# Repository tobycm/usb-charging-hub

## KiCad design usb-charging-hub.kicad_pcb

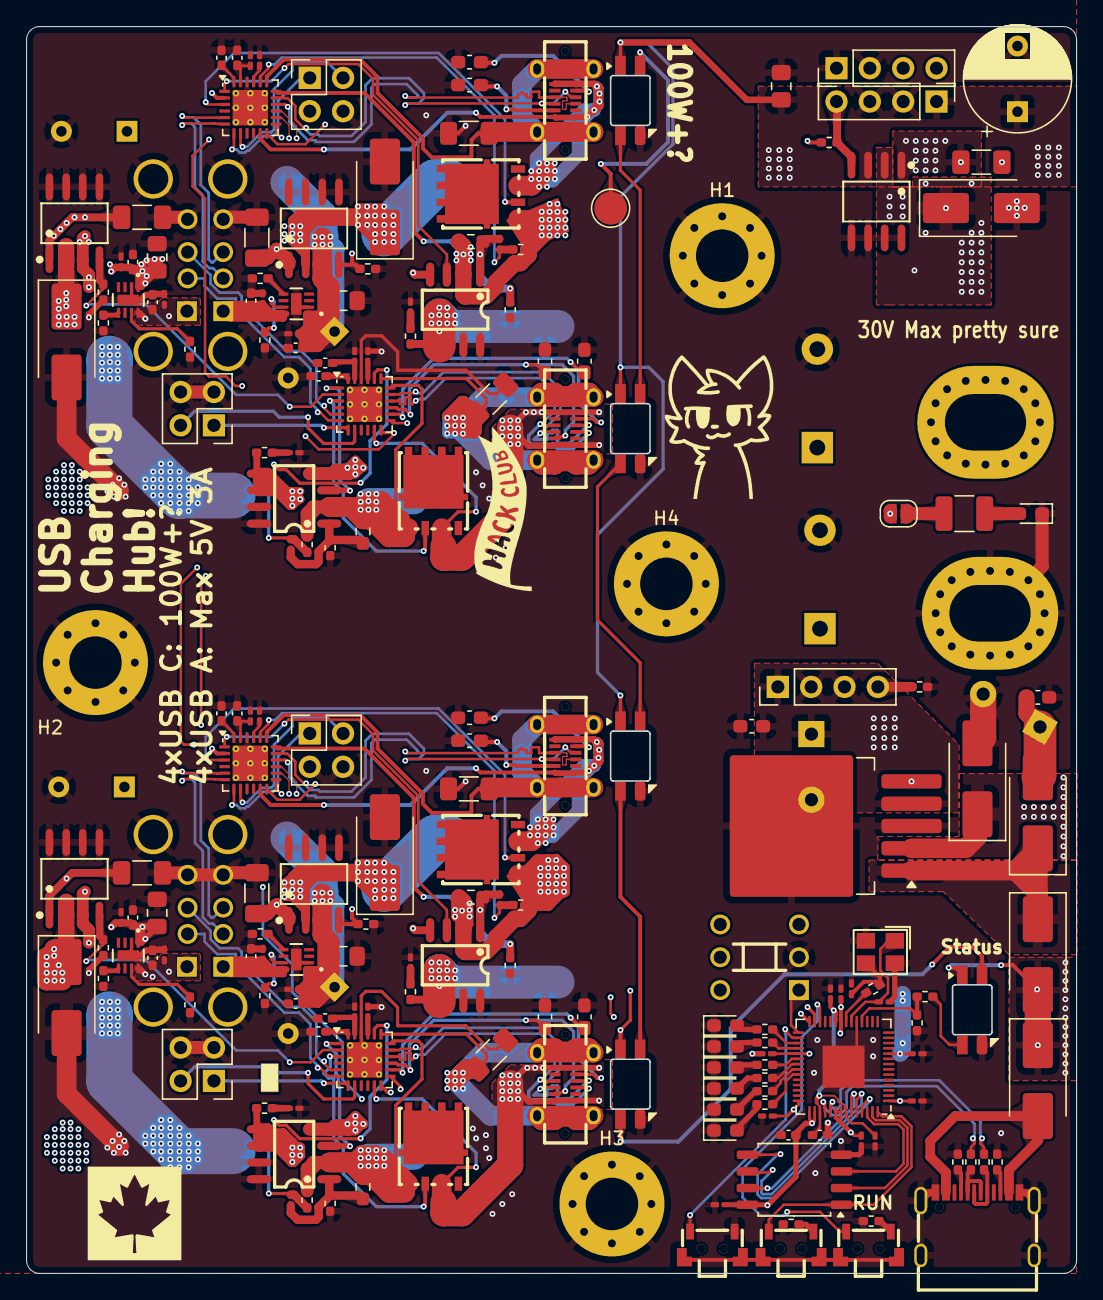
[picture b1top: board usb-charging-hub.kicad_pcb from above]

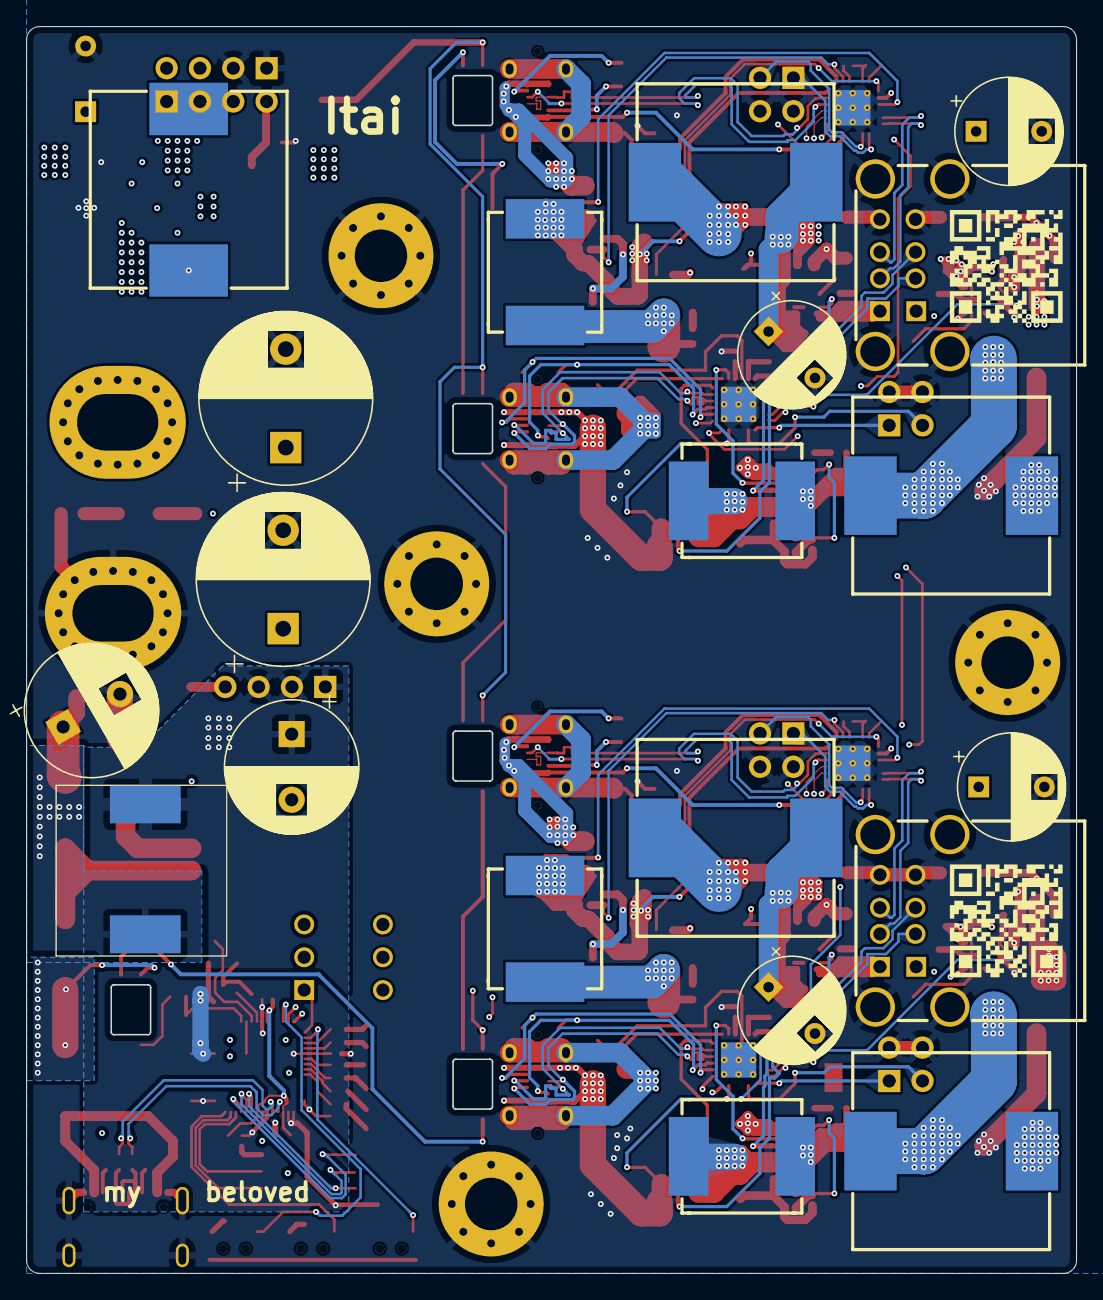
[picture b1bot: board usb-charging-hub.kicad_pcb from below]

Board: 4 copper layers, 80.0 x 95.0 mm, 214 parts (20 on the bottom side), 159 nets.

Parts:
C1, C2: 50V,1000uF; CP_Radial_D13.0mm_P7.50mm
C3, C4, C5, C7, C8, C9, C10, C11, C12, C29, C36, C38, C40, C42, C44, C45, C52, C59, C66, C68, C70, C72, C74, C75, C82: 100nF; C_0201_0603Metric_Pad0.64x0.40mm_HandSolder
C6, C13, C30, C31, C37, C39, C41, C43, C46, C47, C60, C61, C67, C69, C71, C73, C76, C77: 1uF; C_0402_1005Metric_Pad0.74x0.62mm_HandSolder
C14, C15: 18pF; C_0201_0603Metric_Pad0.64x0.40mm_HandSolder
C16: 50V,470uF; CP_Radial_D10.0mm_P5.00mm
C17: 50V,1uF; C_0603_1608Metric_Pad1.08x0.95mm_HandSolder
C18: 35V,470uF; CP_Radial_D10.0mm_P5.00mm
C19: 10V,10uF; C_0603_1608Metric_Pad1.08x0.95mm_HandSolder
C20, C23, C24, C53, C54: 50V,10uF; C_1206_3216Metric_Pad1.33x1.80mm_HandSolder
C21, C25, C27, C55, C57: 35V,180uF; CP_Radial_D8.0mm_P5.00mm
C22, C26, C28, C56, C58: 35V,22uF; C_0805_2012Metric_Pad1.18x1.45mm_HandSolder
C32, C33, C48, C49, C62, C63, C78, C79: 390pF 5% X7R; C_0603_1608Metric_Pad1.08x0.95mm_HandSolder
C34, C50, C64, C80: 100pF; C_0201_0603Metric_Pad0.64x0.40mm_HandSolder
C35, C51, C65, C81: 1nF; C_0201_0603Metric_Pad0.64x0.40mm_HandSolder
D1: LED; LED_0603_1608Metric_Pad1.05x0.95mm_HandSolder
D2, D3: Green; LED_0603_1608Metric_Pad1.05x0.95mm_HandSolder
D4, D9, D11, D12, D13, D14, D15, D16: 40V,10A; D_SMB_Handsoldering
D5, D6: Amber; LED_0603_1608Metric_Pad1.05x0.95mm_HandSolder
D7, D8: Red; LED_0603_1608Metric_Pad1.05x0.95mm_HandSolder
D10: 60V,10A; D_SMB_Handsoldering
H1, H2, H3, H4: MountingHole_Pad; MountingHole_4mm_Pad_Via
J1, J2: Conn_01x01_Pin; MountingHole_4.3x6.2mm_M4_Pad_Via
J4, J6, J7: Conn_01x04_Pin; PinHeader_1x04_P2.54mm_Vertical
J8, J11, J13, J16: TYPE-C 16PLT-H10.0; TYPE-C-SMD_USB4120-03-C
J9, J12, J14, J17: Conn_01x04_Pin; PinHeader_2x02_P2.54mm_Vertical
J10, J15: XDUF-0426-081_C18202150; USB-A-TH_XDUF-0426-081
J35: GT-USB-7010ASV; USB-C-SMD_G-SWITCH_GT-USB-7010ASV
JP1: SolderJumper_2_Open; SolderJumper-2_P1.3mm_Open_RoundedPad1.0x1.5mm
L1: 33uH,4.25A; SDRI129-330MT
L2, L3, L4, L7, L8: YPRH1508-680M; IND-SMD_L15.0-W15.0
L5, L6, L9, L10: 6.8uH,5.2A,8A(Isat); IND-SMD_L8.0-W8.0-1
LED1, LED2, LED3, LED4, LED5: SK6812MINI-E_C5149201; SK6812-MINI-E
Q1, Q2, Q3, Q4: PMOS; PDFN-8_L5.2-W5.9-P1.27-LS6.2-BL
R1: 1.5k; R_1210_3225Metric_Pad1.30x2.65mm_HandSolder
R2, R3: 5.1k; R_0402_1005Metric_Pad0.72x0.64mm_HandSolder
R4, R5: 27; R_0402_1005Metric_Pad0.72x0.64mm_HandSolder
R6, R11, R16, R22, R31, R38, R47: 1k; R_0402_1005Metric_Pad0.72x0.64mm_HandSolder
R9, R10, R12, R13, R14, R15, R107: 470; R_0402_1005Metric_Pad0.72x0.64mm_HandSolder
R17, R18, R19, R20, R35, R36: 100k; R_0402_1005Metric_Pad0.72x0.64mm_HandSolder
R21, R30, R37, R46: 40k; R_0603_1608Metric_Pad0.98x0.95mm_HandSolder
R23, R32, R39, R48: 6.8; R_0402_1005Metric_Pad0.72x0.64mm_HandSolder
R24, R27, R29, R33, R40, R43, R45, R49, R108: 10k; R_0402_1005Metric_Pad0.72x0.64mm_HandSolder
R25, R34, R41, R50: 5mOhm 1% Shunt; R_1206_3216Metric_Pad1.30x1.75mm_HandSolder
R26, R28, R42, R44: 249k; R_0402_1005Metric_Pad0.72x0.64mm_HandSolder
SW1, SW3, SW4: TS24CA; SW-SMD_TS24CA
SW2: Latching; SW-TH_6P-L8.0-W8.0-P2.50
TP1: TestPoint; TestPoint_Pad_D2.5mm
U1: W25Q32JVSS; SOIC-8_5.3x5.3mm_P1.27mm
U2: ABM8-272-T3_C20625731; CRYSTAL-SMD_4P-L3.2-W2.5-BL
U3: RP2040; QFN-56-1EP_7x7mm_P0.4mm_EP3.2x3.2mm
U4: LM2596S-3.3; TO-263-5_TabPin3
U5, U6, U7, U14, U15: XXL1509-5.0; SOIC-8_L4.9-W3.9-P1.27-LS6.0-BL
U8, U12, U16, U20: NDP23511KC; SOP-8_L4.9-W3.9-P1.27-LS6.0-BL
U9, U13, U17, U21: CYPD3175-24LQXQ; QFN-24-1EP_4x4mm_P0.5mm_EP2.7x2.7mm_ThermalVias
U10, U11, U18, U19: LS0505EVD22; LS0505EVD22_LTF

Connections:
3.3V_BUCK_EN: J4.4, R17.2, U4.5 (~ON/OFF)
5V_BUCK_EN: J6.4, R18.2, U5.4 (EN)
+1V1: C4.2, C5.2, C6.2, U3.23 (DVDD), U3.45 (VREG_VOUT), U3.50 (DVDD)
+3.3V: C3.2, C7.2, C8.2, C9.2, C10.2, C11.2, C12.2, C13.2, C18.1, C19.1, J4.1, J4.2, J4.3, L1.2, U1.8 (VCC), U3.1 (IOVDD), U3.10 (IOVDD), U3.22 (IOVDD), U3.33 (IOVDD), U3.42 (IOVDD), U3.43 (ADC_AVDD), U3.44 (VREG_IN), U3.48 (USB_VDD), U3.49 (IOVDD), U4.4 (FB)
+5V: C21.1, C22.1, D4.1 (K), D9.2 (A), J6.1, J6.2, J6.3, L2.2, LED1.1 (VDD), LED2.1 (VDD), LED3.1 (VDD), LED4.1 (VDD), LED5.1 (VDD), U5.3 (FB)
/USB 1/1_BUCK_EN: U8.3 (EN), U9.1 (P1.0)
/USB 1/1_D+: J8.A6 (DP1), J8.B6 (DP2), U9.17 (DP0/P3.0)
/USB 1/1_D-: J8.A7 (DN1), J8.B7 (DN2), U9.16 (DM0/P3.1)
/USB 1/2_BUCK_EN: U12.3 (EN), U13.1 (P1.0)
/USB 1/2_D+: J11.A6 (DP1), J11.B6 (DP2), U13.17 (DP0/P3.0)
/USB 1/2_D-: J11.A7 (DN1), J11.B7 (DN2), U13.16 (DM0/P3.1)
/USB 1/D_5V: C27.1, C28.1, C43.2, C44.2, L4.2, U7.3 (FB), U11.1 (IN)
/USB 1/D_BUCK_EN: R20.2, U7.4 (EN), U13.2 (P1.1)
/USB 1/D_D+: J10.7 (D-D+), U13.5 (DP1/P1.2)
/USB 1/D_D-: J10.6 (D-D-), U13.6 (DM1/P1.3)
/USB 1/D_EN: R29.1, U11.5 (EN)
/USB 1/U_5V: C25.1, C26.1, C39.2, C40.2, L3.2, U6.3 (FB), U10.1 (IN)
/USB 1/U_BUCK_EN: R19.2, U6.4 (EN), U9.2 (P1.1)
/USB 1/U_D+: J10.3 (U-D+), U9.5 (DP1/P1.2)
/USB 1/U_D-: J10.2 (U-D-), U9.6 (DM1/P1.3)
/USB 1/U_EN: R27.1, U10.5 (EN)
/USB 2/1_BUCK_EN: U16.3 (EN), U17.1 (P1.0)
/USB 2/1_D+: J13.A6 (DP1), J13.B6 (DP2), U17.17 (DP0/P3.0)
/USB 2/1_D-: J13.A7 (DN1), J13.B7 (DN2), U17.16 (DM0/P3.1)
/USB 2/2_BUCK_EN: U20.3 (EN), U21.1 (P1.0)
/USB 2/2_D+: J16.A6 (DP1), J16.B6 (DP2), U21.17 (DP0/P3.0)
/USB 2/2_D-: J16.A7 (DN1), J16.B7 (DN2), U21.16 (DM0/P3.1)
/USB 2/D_5V: C57.1, C58.1, C73.2, C74.2, L8.2, U15.3 (FB), U19.1 (IN)
/USB 2/D_BUCK_EN: R36.2, U15.4 (EN), U21.2 (P1.1)
/USB 2/D_D+: J15.7 (D-D+), U21.5 (DP1/P1.2)
/USB 2/D_D-: J15.6 (D-D-), U21.6 (DM1/P1.3)
/USB 2/D_EN: R45.1, U19.5 (EN)
/USB 2/U_5V: C55.1, C56.1, C69.2, C70.2, L7.2, U14.3 (FB), U18.1 (IN)
/USB 2/U_BUCK_EN: R35.2, U14.4 (EN), U17.2 (P1.1)
/USB 2/U_D+: J15.3 (U-D+), U17.5 (DP1/P1.2)
/USB 2/U_D-: J15.2 (U-D-), U17.6 (DM1/P1.3)
/USB 2/U_EN: R43.1, U18.5 (EN)
/rp2040/USB_D+: R4.2, U3.47 (USB_DP)
/rp2040/USB_D-: R5.2, U3.46 (USB_DM)
/rp2040/USB_R_D+: J35.A6 (DP1), J35.B6 (DP2), R4.1
/rp2040/USB_R_D-: J35.A7 (DN1), J35.B7 (DN2), R5.1
GND: C1.2, C2.2, C3.1, C4.1, C5.1, C6.1, C7.1, C8.1, C9.1, C10.1, C11.1, C12.1, C13.1, C14.1, C15.1, C16.2, C17.2, C18.2, C19.2, C20.2, C21.2, C22.2, C23.2, C24.2, C25.2, C26.2, C27.2, C28.2, C29.1, C30.1, C31.1, C32.2, C33.2, C35.2, C36.2, C37.1, C38.1, C39.1, C40.1, C41.1, C42.1, C43.1, C44.1, C45.1, C46.1, C47.1, C48.2, C49.2, C51.2, C52.2, C53.2, C54.2, C55.2, C56.2, C57.2, C58.2, C59.1, C60.1, C61.1, C62.2, C63.2, C65.2, C66.2, C67.1, C68.1, C69.1, C70.1, C71.1, C72.1, C73.1, C74.1, C75.1, C76.1, C77.1, C78.2, C79.2, C81.2, C82.2, D1.1 (K), D2.1 (K), D3.1 (K), D5.1 (K), D6.1 (K), D7.1 (K), D8.1 (K), D11.2 (A), D12.2 (A), D13.2 (A), D14.2 (A), D15.2 (A), D16.2 (A), H1.1, H2.1, H3.1, H4.1, J2.1, J7.1, J7.2, J9.3, J9.4, J10.4 (U-GND), J10.8 (D-GND), J10.9 (SHELL), J10.10 (SHELL), J10.11 (SHELL), J10.12 (SHELL), J12.3, J12.4, J14.3, J14.4, J15.4 (U-GND), J15.8 (D-GND), J15.9 (SHELL), J15.10 (SHELL), J15.11 (SHELL), J15.12 (SHELL), J17.3, J17.4, J35.1 (SHELL), J35.2 (SHELL), J35.3 (SHELL), J35.4 (SHELL), J35.A1B12 (GND), J35.B1A12 (GND), LED1.3 (GND), LED2.3 (GND), LED3.3 (GND), LED4.3 (GND), LED5.3 (GND), R2.2, R3.2, R11.1, R16.1, R17.1, R18.1, R19.1, R20.1, R24.2, R25.2, R26.2, R27.2, R28.2, R29.2, R33.2, R35.1, R36.1, R40.2, R41.2, R42.2, R43.2, R44.2, R45.2, R49.2, R50.2, R108.2, SW1.1, SW1.2, SW1.3, SW2.2, SW3.1, SW3.2, SW4.1, SW4.2, U1.4 (GND), U2.2 (GND), U2.4 (GND), U3.19 (TESTEN), U3.57 (GND), U4.3 (GND), U5.5 (GND), U5.6 (GND), U5.7 (GND), U5.8 (GND), U6.5 (GND), U6.6 (GND), U6.7 (GND), U6.8 (GND), U7.5 (GND), U7.6 (GND), U7.7 (GND), U7.8 (GND), U8.7 (RT), U8.8 (GND), U9.22 (GND), U9.25 (GND), U10.2 (GND), U10.9 (GND), U11.2 (GND), U11.9 (GND), U12.7 (RT), U12.8 (GND), U14.5 (GND), U14.6 (GND), U14.7 (GND), U14.8 (GND), U15.5 (GND), U15.6 (GND), U15.7 (GND), U15.8 (GND), U16.7 (RT), U16.8 (GND), U17.22 (GND), U17.25 (GND), U18.2 (GND), U18.9 (GND), U19.2 (GND), U19.9 (GND), U20.7 (RT), U20.8 (GND), U21.22 (GND), U21.25 (GND)
unnamed: C14.2, R6.1, U2.3
unnamed: C35.1, R23.2
unnamed: C51.1, R32.2
unnamed: C65.1, R39.2
unnamed: C81.1, R48.2
unnamed: D1.2 (A), R1.2
unnamed: D2.2 (A), R9.2
unnamed: D3.2 (A), R10.2
unnamed: D5.2 (A), R12.2
unnamed: D6.2 (A), R13.2
unnamed: D7.2 (A), R14.2
unnamed: D8.2 (A), R15.2
unnamed: D9.1 (K), D10.1 (K), U4.1 (VIN)
unnamed: D11.1 (K), L1.1, U4.2 (OUT)
unnamed: D12.1 (K), L2.1, U5.2 (OUTPUT)
unnamed: D13.1 (K), L3.1, U6.2 (OUTPUT)
unnamed: D14.1 (K), L4.1, U7.2 (OUTPUT)
unnamed: D15.1 (K), L7.1, U14.2 (OUTPUT)
unnamed: D16.1 (K), L8.1, U15.2 (OUTPUT)
unnamed: C33.1, J8.A5 (CC1), U9.15 (CC1)
unnamed: C32.1, J8.B5 (CC2), U9.14 (CC2)
unnamed: J8.0 (EH), J8.A1 (GND), J8.A12 (GND), J8.B1 (GND), J8.B12 (GND), R25.1, U9.19 (CSP)
unnamed: J9.1, U9.7 (P0.0/SWD_DAT_0)
unnamed: J9.2, U9.8 (P0.1/SWD_CLK_0)
unnamed: C41.2, C42.2, J10.5 (D-VCC), U11.8 (OUT)
unnamed: C37.2, C38.2, J10.1 (U-VCC), U10.8 (OUT)
unnamed: C49.1, J11.A5 (CC1), U13.15 (CC1)
unnamed: C48.1, J11.B5 (CC2), U13.14 (CC2)
unnamed: J11.0 (EH), J11.A1 (GND), J11.A12 (GND), J11.B1 (GND), J11.B12 (GND), R34.1, U13.19 (CSP)
unnamed: J12.1, U13.7 (P0.0/SWD_DAT_0)
unnamed: J12.2, U13.8 (P0.1/SWD_CLK_0)
unnamed: C63.1, J13.A5 (CC1), U17.15 (CC1)
unnamed: C62.1, J13.B5 (CC2), U17.14 (CC2)
unnamed: J13.0 (EH), J13.A1 (GND), J13.A12 (GND), J13.B1 (GND), J13.B12 (GND), R41.1, U17.19 (CSP)
unnamed: J14.1, U17.7 (P0.0/SWD_DAT_0)
unnamed: J14.2, U17.8 (P0.1/SWD_CLK_0)
unnamed: C71.2, C72.2, J15.5 (D-VCC), U19.8 (OUT)
unnamed: C67.2, C68.2, J15.1 (U-VCC), U18.8 (OUT)
unnamed: C79.1, J16.A5 (CC1), U21.15 (CC1)
unnamed: C78.1, J16.B5 (CC2), U21.14 (CC2)
unnamed: J16.0 (EH), J16.A1 (GND), J16.A12 (GND), J16.B1 (GND), J16.B12 (GND), R50.1, U21.19 (CSP)
unnamed: J17.1, U21.7 (P0.0/SWD_DAT_0)
unnamed: J17.2, U21.8 (P0.1/SWD_CLK_0)
unnamed: J35.A5 (CC1), R2.1
unnamed: J35.B5 (CC2), R3.1
unnamed: JP1.1 (A), R1.1
unnamed: L5.1, R23.1, U8.5 (SW), U8.6 (SW)
unnamed: L6.1, R32.1, U12.5 (SW), U12.6 (SW)
unnamed: L9.1, R39.1, U16.5 (SW), U16.6 (SW)
unnamed: L10.1, R48.1, U20.5 (SW), U20.6 (SW)
unnamed: LED1.2 (DOUT), LED2.4 (DIN)
unnamed: LED2.2 (DOUT), LED3.4 (DIN)
unnamed: LED3.2 (DOUT), LED4.4 (DIN)
unnamed: LED4.2 (DOUT), LED5.4 (DIN)
unnamed: LED5.2 (DOUT), TP1.1
unnamed: L5.2, Q1.1 (D), R21.1, R22.1, U8.2 (VSEN), U9.18 (VBUS_IN_DIS)
unnamed: Q1.2 (G), U9.3 (VBUS_P_CTRL)
unnamed: J8.A4 (VBUS), J8.A9 (VBUS), J8.B4 (VBUS), J8.B9 (VBUS), Q1.3 (S), U9.11 (VBUS_C_MON_DIS)
unnamed: L6.2, Q2.1 (D), R30.1, R31.1, U12.2 (VSEN), U13.18 (VBUS_IN_DIS)
unnamed: Q2.2 (G), U13.3 (VBUS_P_CTRL)
unnamed: J11.A4 (VBUS), J11.A9 (VBUS), J11.B4 (VBUS), J11.B9 (VBUS), Q2.3 (S), U13.11 (VBUS_C_MON_DIS)
unnamed: L9.2, Q3.1 (D), R37.1, R38.1, U16.2 (VSEN), U17.18 (VBUS_IN_DIS)
unnamed: Q3.2 (G), U17.3 (VBUS_P_CTRL)
unnamed: J13.A4 (VBUS), J13.A9 (VBUS), J13.B4 (VBUS), J13.B9 (VBUS), Q3.3 (S), U17.11 (VBUS_C_MON_DIS)
unnamed: L10.2, Q4.1 (D), R46.1, R47.1, U20.2 (VSEN), U21.18 (VBUS_IN_DIS)
unnamed: Q4.2 (G), U21.3 (VBUS_P_CTRL)
unnamed: J16.A4 (VBUS), J16.A9 (VBUS), J16.B4 (VBUS), J16.B9 (VBUS), Q4.3 (S), U21.11 (VBUS_C_MON_DIS)
unnamed: R11.2, SW3.3
unnamed: R16.2, SW4.3
unnamed: R34.2, U13.22 (GND), U13.25 (GND)
unnamed: R107.1, R108.1, U3.18 (GPIO15)
unnamed: SW2.1, U3.29 (GPIO18)
unnamed: SW1.4, U3.30 (GPIO19)
unnamed: R9.1, U3.31 (GPIO20)
unnamed: R10.1, U3.32 (GPIO21)
unnamed: R12.1, U3.34 (GPIO22)
unnamed: R13.1, U3.35 (GPIO23)
unnamed: R14.1, U3.36 (GPIO24)
unnamed: R15.1, U3.37 (GPIO25)
unnamed: C34.1, R21.2, R24.1, U8.1 (VFB)
unnamed: C36.1, U9.21 (COMP)
unnamed: C34.2, R22.2, U9.20 (FB)
unnamed: C31.2, U9.24 (VCCD)
unnamed: C29.2, C30.2, U9.23 (VDDD)
unnamed: R26.1, U10.7 (ILIM)
unnamed: R28.1, U11.7 (ILIM)
unnamed: C50.1, R30.2, R33.1, U12.1 (VFB)
unnamed: C52.1, U13.21 (COMP)
unnamed: C50.2, R31.2, U13.20 (FB)
unnamed: C47.2, U13.24 (VCCD)
unnamed: C45.2, C46.2, U13.23 (VDDD)
unnamed: C64.1, R37.2, R40.1, U16.1 (VFB)
unnamed: C66.1, U17.21 (COMP)
unnamed: C64.2, R38.2, U17.20 (FB)
unnamed: C61.2, U17.24 (VCCD)
unnamed: C59.2, C60.2, U17.23 (VDDD)
unnamed: R42.1, U18.7 (ILIM)
unnamed: R44.1, U19.7 (ILIM)
unnamed: C80.1, R46.2, R49.1, U20.1 (VFB)
unnamed: C82.1, U21.21 (COMP)
unnamed: C80.2, R47.2, U21.20 (FB)
unnamed: C77.2, U21.24 (VCCD)
unnamed: C75.2, C76.2, U21.23 (VDDD)
Pixels: LED1.4 (DIN), R107.2
QSPI_SCLK: U1.6 (CLK), U3.52 (QSPI_SCLK)
QSPI_SD0: U1.5 (DI/IO_{0}), U3.53 (QSPI_SD0)
QSPI_SD1: U1.2 (DO/IO_{1}), U3.55 (QSPI_SD1)
QSPI_SD2: U1.3 (~WP/IO_{2}), U3.54 (QSPI_SD2)
QSPI_SD3: U1.7 (~HOLD/~RESET/IO_{3}), U3.51 (QSPI_SD3)
QSPI_SS: SW3.4, U1.1 (~CS), U3.56 (QSPI_SS)
RUN: SW4.4, U3.26 (RUN)
SCL: U3.28 (GPIO17), U9.13 (P2.3), U13.13 (P2.3), U17.13 (P2.3), U21.13 (P2.3)
SDA: U3.27 (GPIO16), U9.12 (P2.2), U13.12 (P2.2), U17.12 (P2.2), U21.12 (P2.2)
VBUS: D4.2 (A), J35.A4B9 (VBUS), J35.B4A9 (VBUS)
VDC: C1.1, C2.1, C16.1, C17.1, C20.1, C23.1, C24.1, C53.1, C54.1, D10.2 (A), J1.1, J7.3, J7.4, JP1.2 (B), U5.1 (VIN), U6.1 (VIN), U7.1 (VIN), U8.4 (VIN), U12.4 (VIN), U14.1 (VIN), U15.1 (VIN), U16.4 (VIN), U20.4 (VIN)
XIN: C15.2, U2.1, U3.20 (XIN)
XOUT: R6.2, U3.21 (XOUT)

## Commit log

2025-04-22 Init commit :D
2025-04-23 import settings from raver board
2025-05-15 bom is 90% finish, just smaller parts to be added if any finished rp microcontroller wiring, next is usb c ics and stuff
2025-05-15 fixed wrong wiring of 5V regulator for rp mcu + added all usb a ports
2025-05-17 gave up on single board, gonna make small modules
2025-05-17 add journal for highway.hackclub.com :D
2025-05-17 journal for yesterday :3
2025-05-18 updated journal, pin headers footprint, etc. added labels to rp2350b, finished pcb routing. time to start on other modules yay
2025-05-18 update journal
2025-05-19 no more modules, its gonna work first try :fire: i love infineon and their ICs so much
2025-05-19 finished schematic yay!! now onto pcb routing :fire:
2025-05-20 made huge progress today, finished wiring up the rp2040, finished one usb a and usb c layout :fire::fire::fire:
2025-05-25 holyyy i actually finished all of the bare pcb adding lots of art soon:tm:
2025-05-26 fix some errors and add some art :3
2026-04-25 update schematic
